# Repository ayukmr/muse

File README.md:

# muse

Small device for outputting MIDI, with a rotary encoder, buttons, and an OLED screen.

The board is controlled by a XIAO RP2040 and uses USB-C for both power and data.
A slide switch selects between two modes.
In assign mode, the rotary encoder is used to select notes on the OLED screen and the buttons store the current note.
In play mode, pressing a button sends its assigned note.

This is intended as a simpler hand-solderable board and as a small trinket.

## Schematic

## PCB

## BOM

| Reference           | Qty | Value           | DigiKey Part #         | $     |
|:--------------------|:----|:----------------|:-----------------------|:------|
| J1                  | 1   | Conn_01x04      | [MTLW-104-05-G-S-170-ND](https://digikey.com/en/products/detail/MTLW-104-05-G-S-170) | $1.16 |
| SW1                 | 1   | RotaryEncoder   | [PEC11S-9213K-S0015-ND](https://digikey.com/en/products/detail/PEC11S-9213K-S0015)  | $3.29 |
| SW2                 | 1   | SW_Push         | [401-2002-1-ND](https://digikey.com/en/products/detail/JS202011SCQN)          | $0.87 |
| SW3,SW4,SW5,SW6,SW7 | 5   | SW_Push         | [39-B3FS-4092P-BCT-ND](https://digikey.com/en/products/detail/B3FS-4092P-B/25821304)   | $4.96 |
| U1                  | 1   | XIAO-RP2040-SMD | [1597-102010428-ND](https://digikey.com/en/products/detail/102010428)      | $4.88 |

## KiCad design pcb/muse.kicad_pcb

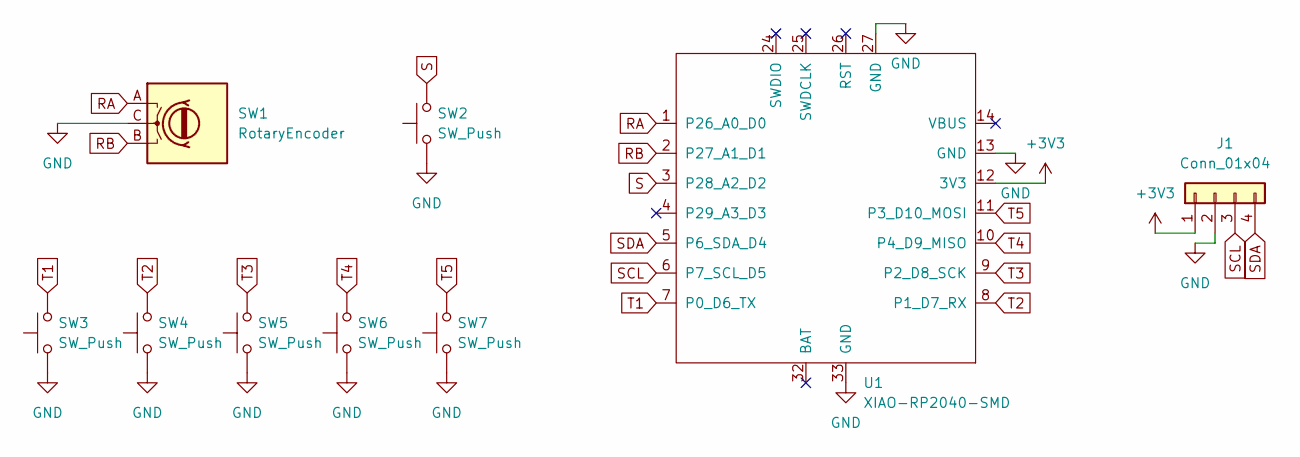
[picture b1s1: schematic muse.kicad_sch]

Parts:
J1: Conn_01x04; DFR0648
SW1: RotaryEncoder; PEC11S929KN0015
SW2: SW_Push; JS202011SCQN
SW3, SW4, SW5, SW6, SW7: SW_Push; B3FS4092PB
U1: XIAO-RP2040-SMD

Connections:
+3V3: J1.1, U1.12 (3V3)
GND: J1.2, SW1.C, SW2.1, SW3.1, SW4.1, SW5.1, SW6.1, SW7.1, U1.13 (GND), U1.27 (GND), U1.33 (GND)
RA: SW1.A, U1.1 (P26_A0_D0)
RB: SW1.B, U1.2 (P27_A1_D1)
S: SW2.2, U1.3 (P28_A2_D2)
SCL: J1.3, U1.6 (P7_SCL_D5)
SDA: J1.4, U1.5 (P6_SDA_D4)
T1: SW3.2, U1.7 (P0_D6_TX)
T2: SW4.2, U1.8 (P1_D7_RX)
T3: SW5.2, U1.9 (P2_D8_SCK)
T4: SW6.2, U1.10 (P4_D9_MISO)
T5: SW7.2, U1.11 (P3_D10_MOSI)

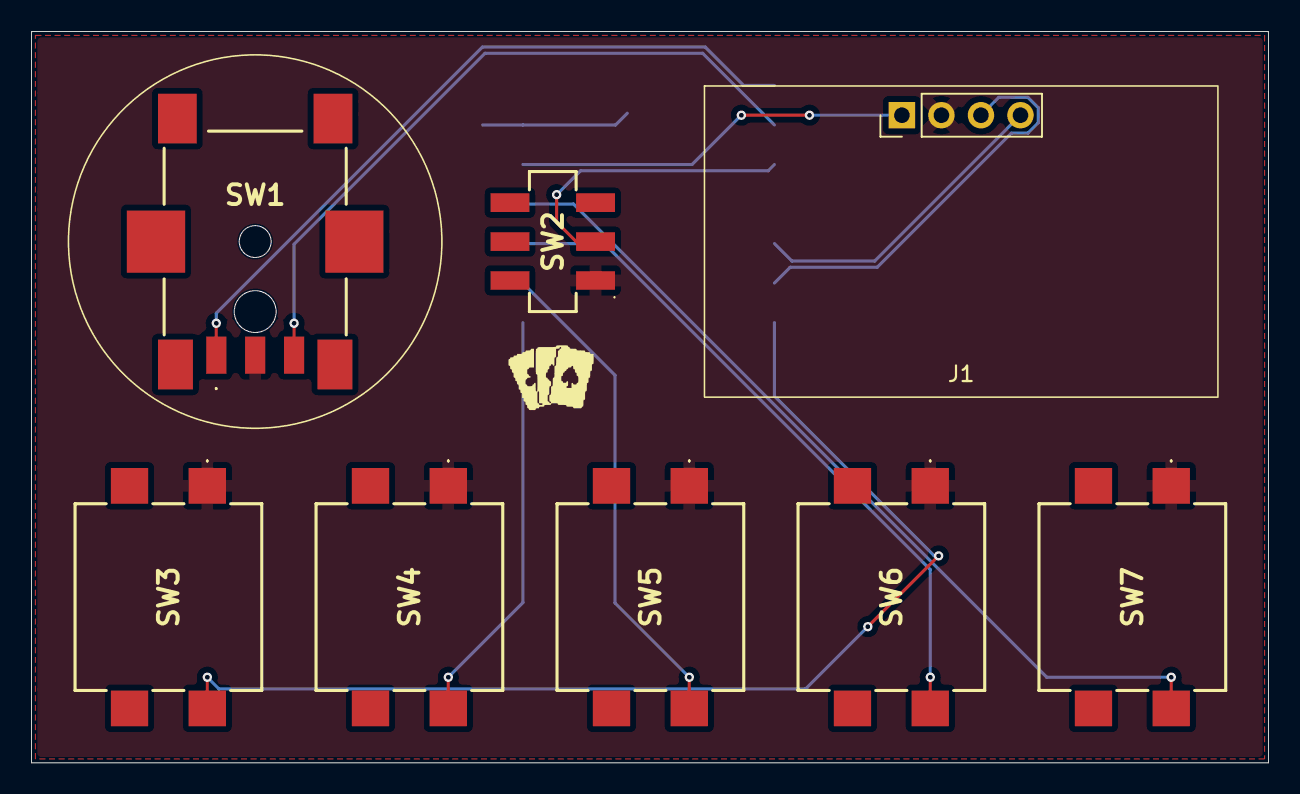
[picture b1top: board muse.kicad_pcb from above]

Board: 2 copper layers, 79.5 x 47.0 mm, 9 parts (1 on the bottom side), 12 nets.

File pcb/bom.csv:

Reference,Qty,Value,Footprint,DigiKey Part #,Link
J1,1,Conn_01x04,Project:DFR0648,MTLW-104-05-G-S-170-ND,https://digikey.com/en/products/detail/MTLW-104-05-G-S-170
SW1,1,RotaryEncoder,Project:PEC11S929KN0015,PEC11S-9213K-S0015-ND,https://digikey.com/en/products/detail/PEC11S-9213K-S0015
SW2,1,SW_Push,Project:JS202011SCQN,401-2002-1-ND,https://digikey.com/en/products/detail/JS202011SCQN
"SW3,SW4,SW5,SW6,SW7",5,SW_Push,Project:B3FS4092PB,39-B3FS-4092P-BCT-ND,https://digikey.com/en/products/detail/B3FS-4092P-B/25821304
U1,1,XIAO-RP2040-SMD,Project:XIAO-RP2040-SMD,1597-102010428-ND,https://digikey.com/en/products/detail/102010428

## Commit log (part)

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2026-06-10 Initialize repo
2026-06-10 Add README
2026-06-10 Update footprint
2026-06-10 Add logo
2026-06-11 Add BOM
2026-06-14 Add testing firmware
2026-06-14 Format README
2026-06-16 Add links to BOM
